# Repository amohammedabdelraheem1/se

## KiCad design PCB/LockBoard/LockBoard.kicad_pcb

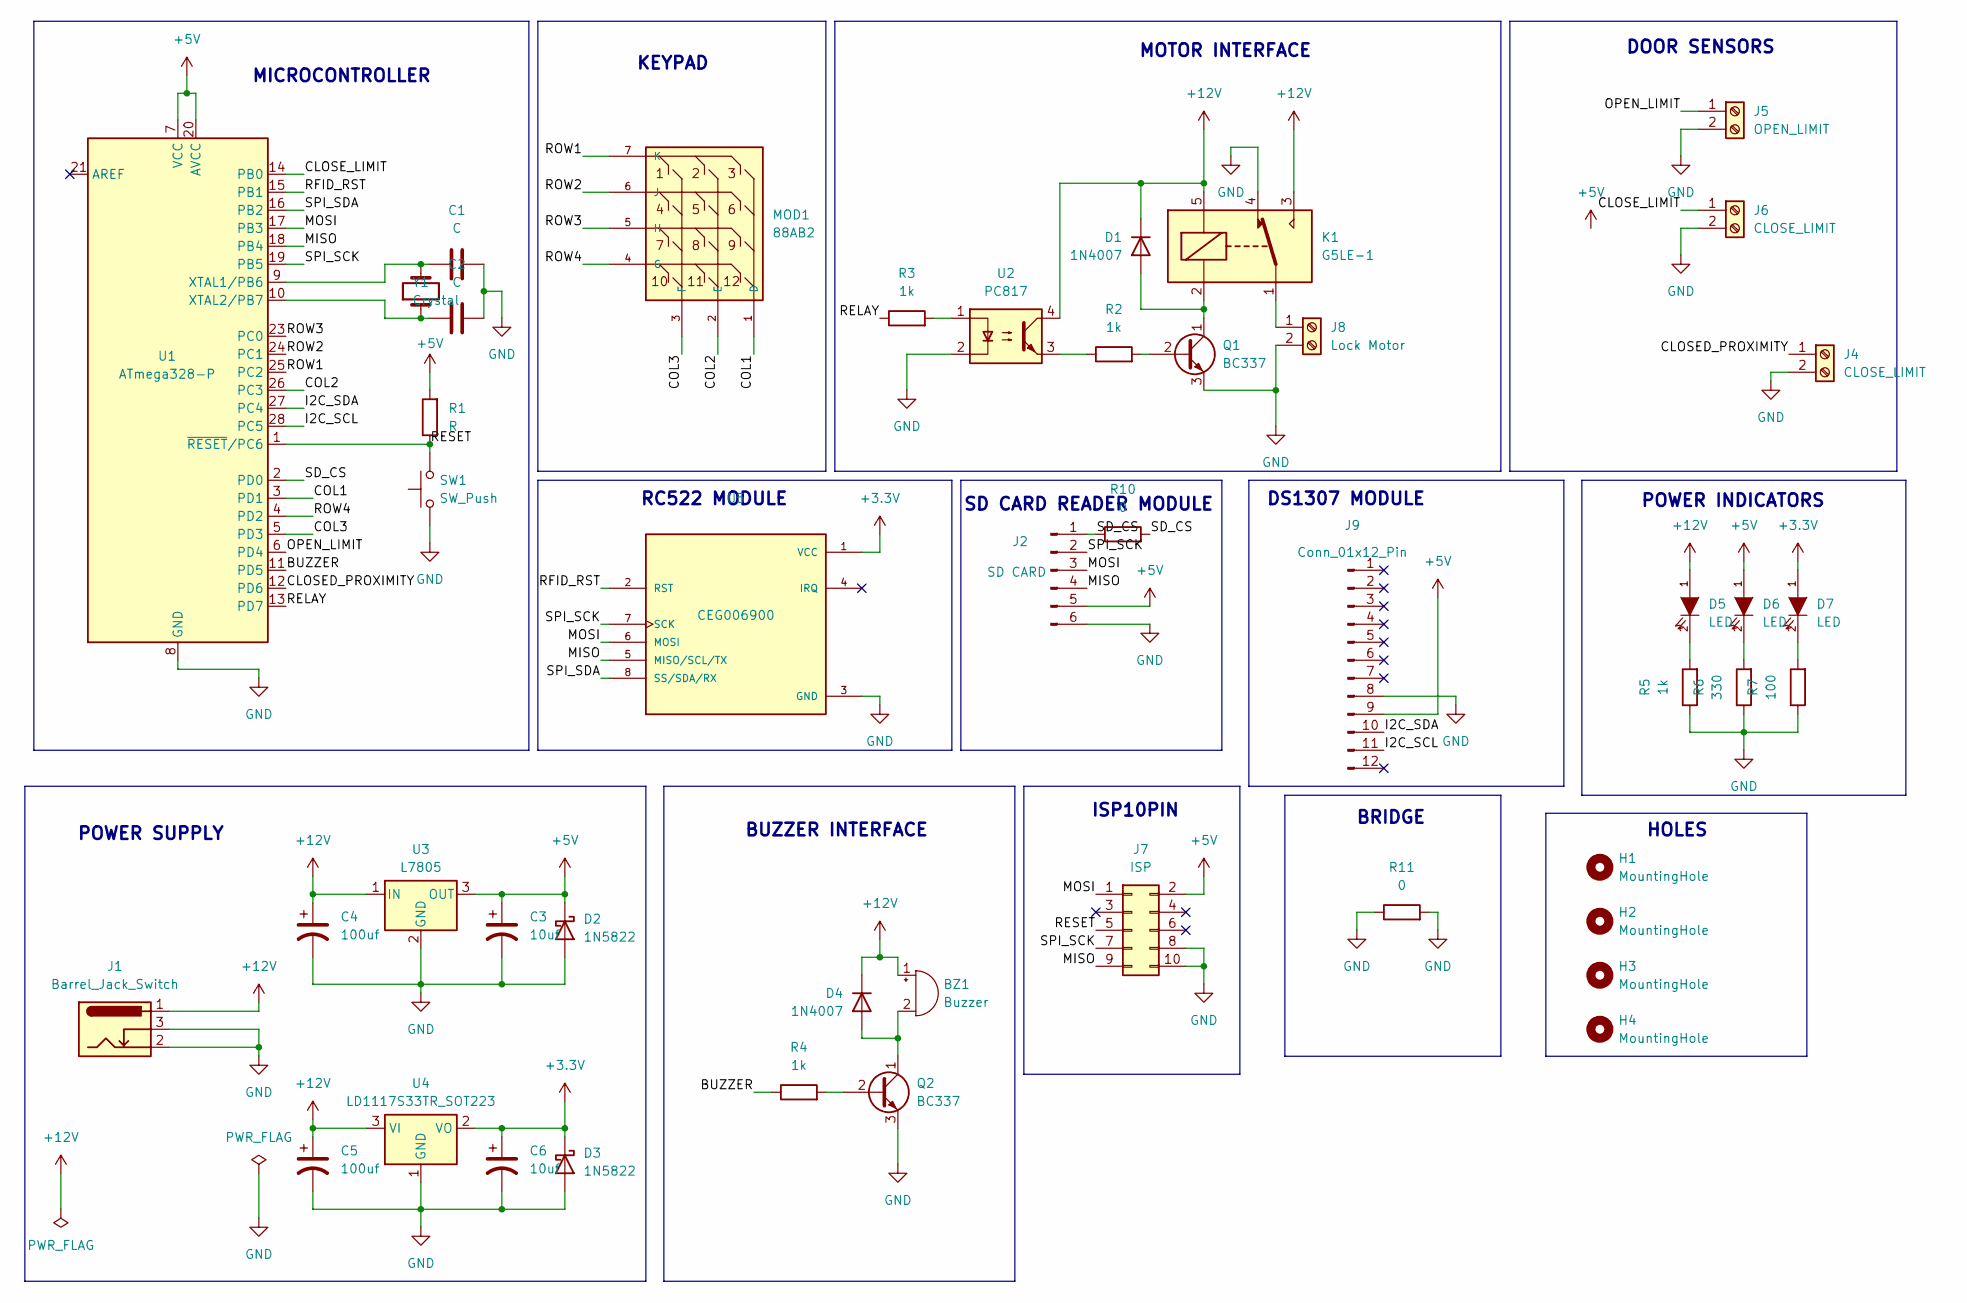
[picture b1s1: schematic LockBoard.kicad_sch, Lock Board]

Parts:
BZ1: Buzzer; Buzzer_12x9.5RM7.6
C1, C2: C; C_Disc_D4.3mm_W1.9mm_P5.00mm
C3, C6: 10uf; CP_Radial_D5.0mm_P2.50mm
C4, C5: 100uf; CP_Radial_D8.0mm_P2.50mm
D1, D4: 1N4007; D_DO-41_SOD81_P10.16mm_Horizontal
D2, D3: 1N5822; D_DO-201AD_P15.24mm_Horizontal
D5, D6, D7: LED; LED_D3.0mm
H1, H2, H3, H4: MountingHole; MountingHole_4.3mm_M4_ISO14580
J1: Barrel_Jack_Switch; BarrelJack_Horizontal
J2: SD CARD; SD_Card_Module
J4, J6: CLOSE_LIMIT; TerminalBlock_Phoenix_MKDS-1,5-2_1x02_P5.00mm_Horizontal
J5: OPEN_LIMIT; TerminalBlock_Phoenix_MKDS-1,5-2_1x02_P5.00mm_Horizontal
J7: ISP; IDC-Header_2x05_P2.54mm_Vertical
J8: Lock Motor; TerminalBlock_Phoenix_MKDS-1,5-2_1x02_P5.00mm_Horizontal
J9: Conn_01x12_Pin; Tiny_RTC_DS1307
K1: G5LE-1; Relay_SPDT_Omron-G5LE-1
MOD1: 88AB2; JST_XH_S7B-XH-A-1_1x07_P2.50mm_Horizontal
Q1, Q2: BC337; TO-92_Inline
R1: R; R_Axial_DIN0207_L6.3mm_D2.5mm_P7.62mm_Horizontal
R2, R3, R4, R5: 1k; R_Axial_DIN0207_L6.3mm_D2.5mm_P7.62mm_Horizontal
R6: 330; R_Axial_DIN0207_L6.3mm_D2.5mm_P7.62mm_Horizontal
R7: 100; R_Axial_DIN0207_L6.3mm_D2.5mm_P7.62mm_Horizontal
R10, R11: 0; R_Axial_DIN0207_L6.3mm_D2.5mm_P7.62mm_Horizontal
SW1: SW_Push; SW_PUSH_6mm
U1: ATmega328-P; DIP-28_W7.62mm
U2: PC817; DIP-4_W7.62mm
U3: L7805; TO-220-3_Vertical
U4: LD1117S33TR_SOT223; TO-220-3_Vertical
U5: CEG006900; JST_XH_S8B-XH-A-1_1x08_P2.50mm_Horizontal; PARTREV 12 June 2019
Y1: Crystal; Crystal_HC49-4H_Vertical

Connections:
+3.3V: C6.1, D3.1 (K), D7.1 (A), U4.2 (VO), U5.1 (VCC)
+5V: C3.1, D2.1 (K), D6.1 (A), J2.5, J7.2, J9.9, R1.2, U1.7 (VCC), U1.20 (AVCC), U3.3 (OUT)
+12V: BZ1.1 (+), C4.1, C5.1, D1.1 (K), D4.1 (K), D5.1 (A), J1.1, K1.3, K1.5, U2.4, U3.1 (IN), U4.3 (VI)
/BUZZER: R4.1, U1.11 (PD5)
/CLOSED_PROXIMITY: J4.1, U1.12 (PD6); also elsewhere on the board
/CLOSE_LIMIT: J6.1, U1.14 (PB0)
/COL1: MOD1.1 (D), U1.3 (PD1)
/COL2: MOD1.2 (E), U1.26 (PC3)
/COL3: MOD1.3 (F), U1.5 (PD3)
/I2C_SCL: J9.11, U1.28 (PC5)
/I2C_SDA: J9.10, U1.27 (PC4)
/MISO: J2.4, J7.9, U1.18 (PB4), U5.5 (MISO/SCL/TX)
/MOSI: J2.3, J7.1, U1.17 (PB3), U5.6 (MOSI)
/OPEN_LIMIT: J5.1, U1.6 (PD4)
/RELAY: R3.1, U1.13 (PD7)
/RESET: J7.5, R1.1, SW1.2, U1.1 (~RESET/PC6)
/RFID_RST: U1.15 (PB1), U5.2 (RST)
/ROW1: MOD1.7 (K), U1.25 (PC2)
/ROW2: MOD1.6 (J), U1.24 (PC1)
/ROW3: MOD1.5 (H), U1.23 (PC0)
/ROW4: MOD1.4 (G), U1.4 (PD2)
/SD_CS: J2.1, R10.1, R10.2, U1.2 (PD0)
/SPI_SCK: J2.2, J7.7, U1.19 (PB5), U5.7 (SCK)
/SPI_SDA: U1.16 (PB2), U5.8 (SS/SDA/RX)
GND: C1.2, C2.2, C3.2, C4.2, C5.2, C6.2, D2.2 (A), D3.2 (A), J1.2, J1.3, J2.6, J4.2, J5.2, J6.2, J7.8, J7.10, J8.2, J9.8, K1.4, Q1.3 (E), Q2.3 (E), R5.1, R6.1, R7.1, R11.1, R11.2, SW1.1, U1.8 (GND), U1.22 (GND), U2.2, U3.2 (GND), U4.1 (GND), U5.3 (GND); also elsewhere on the board
unnamed: BZ1.2 (-), D4.2 (A), Q2.1 (C)
unnamed: D1.2 (A), K1.2, Q1.1 (C)
unnamed: D5.2 (K), R5.2
unnamed: D6.2 (K), R6.2
unnamed: D7.2 (K), R7.2
unnamed: J8.1, K1.1
unnamed: Q1.2 (B), R2.2
unnamed: Q2.2 (B), R4.2
unnamed: R2.1, U2.3
unnamed: R3.2, U2.1
unnamed: C1.1, U1.9 (XTAL1/PB6), Y1.2
unnamed: C2.1, U1.10 (XTAL2/PB7), Y1.1

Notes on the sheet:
MOTOR INTERFACE
HOLES
BRIDGE
POWER SUPPLY
POWER INDICATORS
ISP10PIN
BUZZER INTERFACE
DOOR SENSORS
SD CARD READER MODULE
RC522 MODULE
DS1307 MODULE
MICROCONTROLLER
KEYPAD

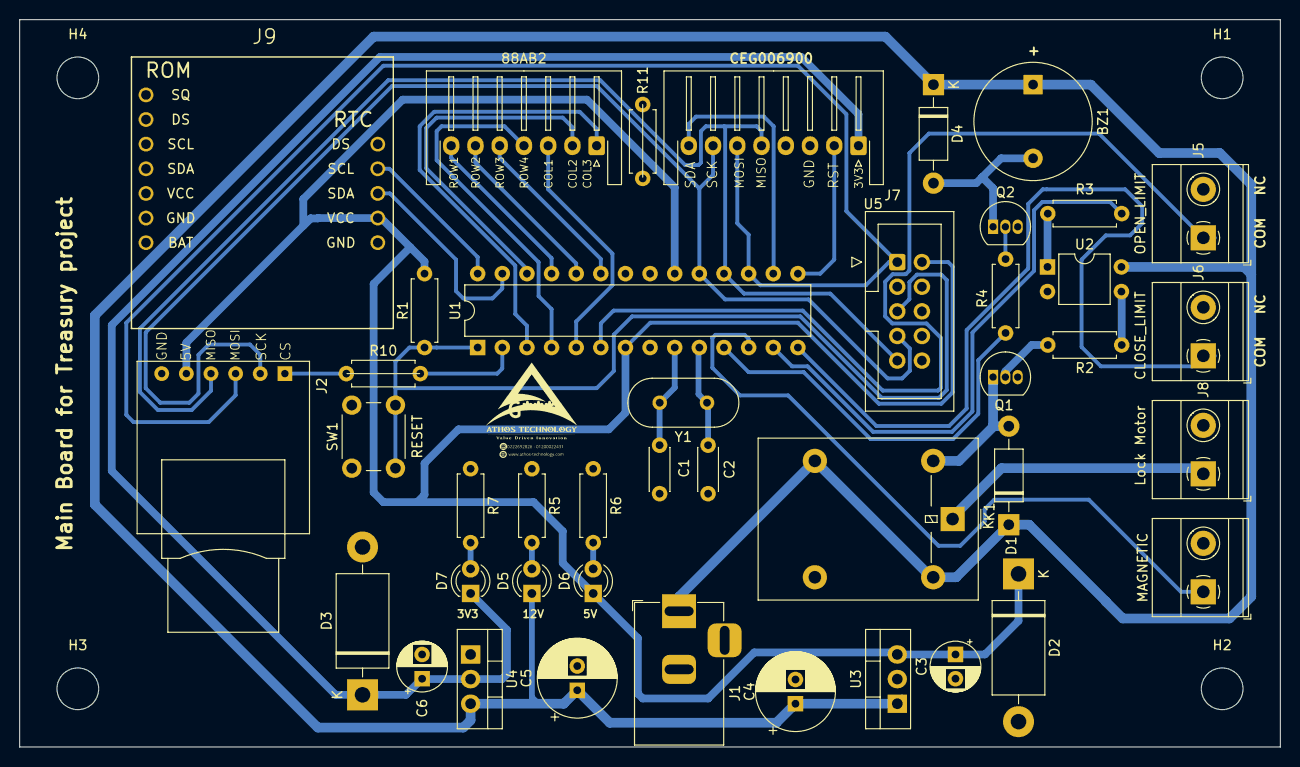
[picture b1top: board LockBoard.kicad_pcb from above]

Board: 2 copper layers, 130.0 x 75.0 mm, 46 parts (0 on the bottom side), 37 nets.

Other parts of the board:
MAGNETIC: CLOSE_LIMIT; TerminalBlock_Phoenix_MKDS-1,5-2_1x02_P5.00mm_Horizontal

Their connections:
/CLOSED_PROXIMITY: MAGNETIC.1; also elsewhere on the board
GND: MAGNETIC.2; also elsewhere on the board

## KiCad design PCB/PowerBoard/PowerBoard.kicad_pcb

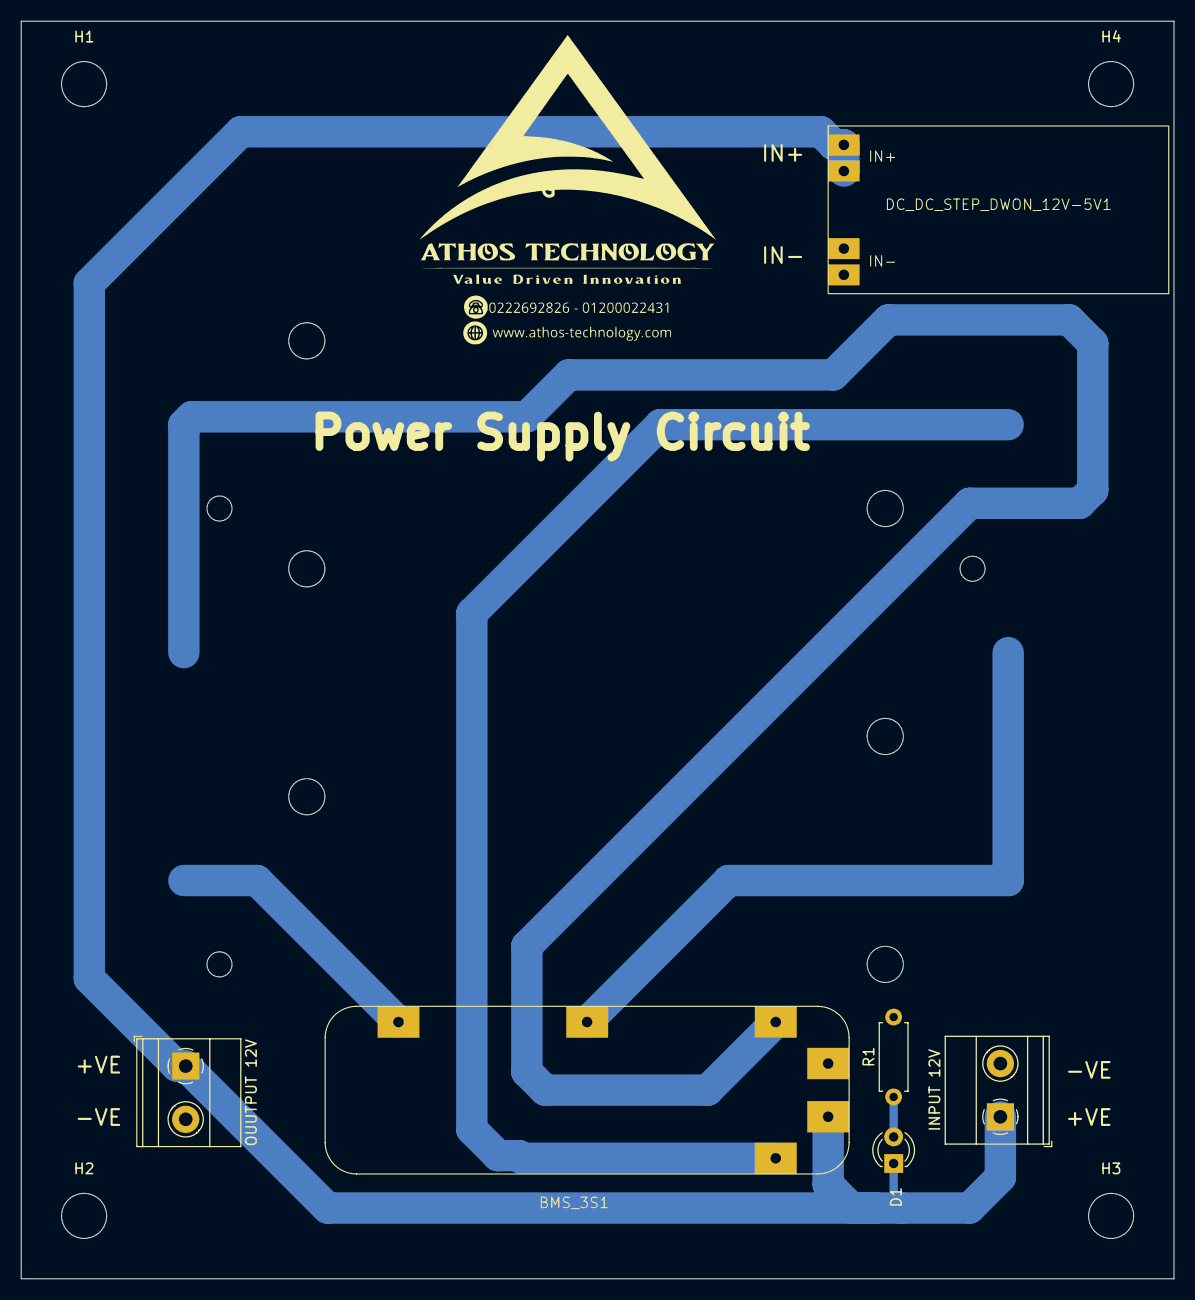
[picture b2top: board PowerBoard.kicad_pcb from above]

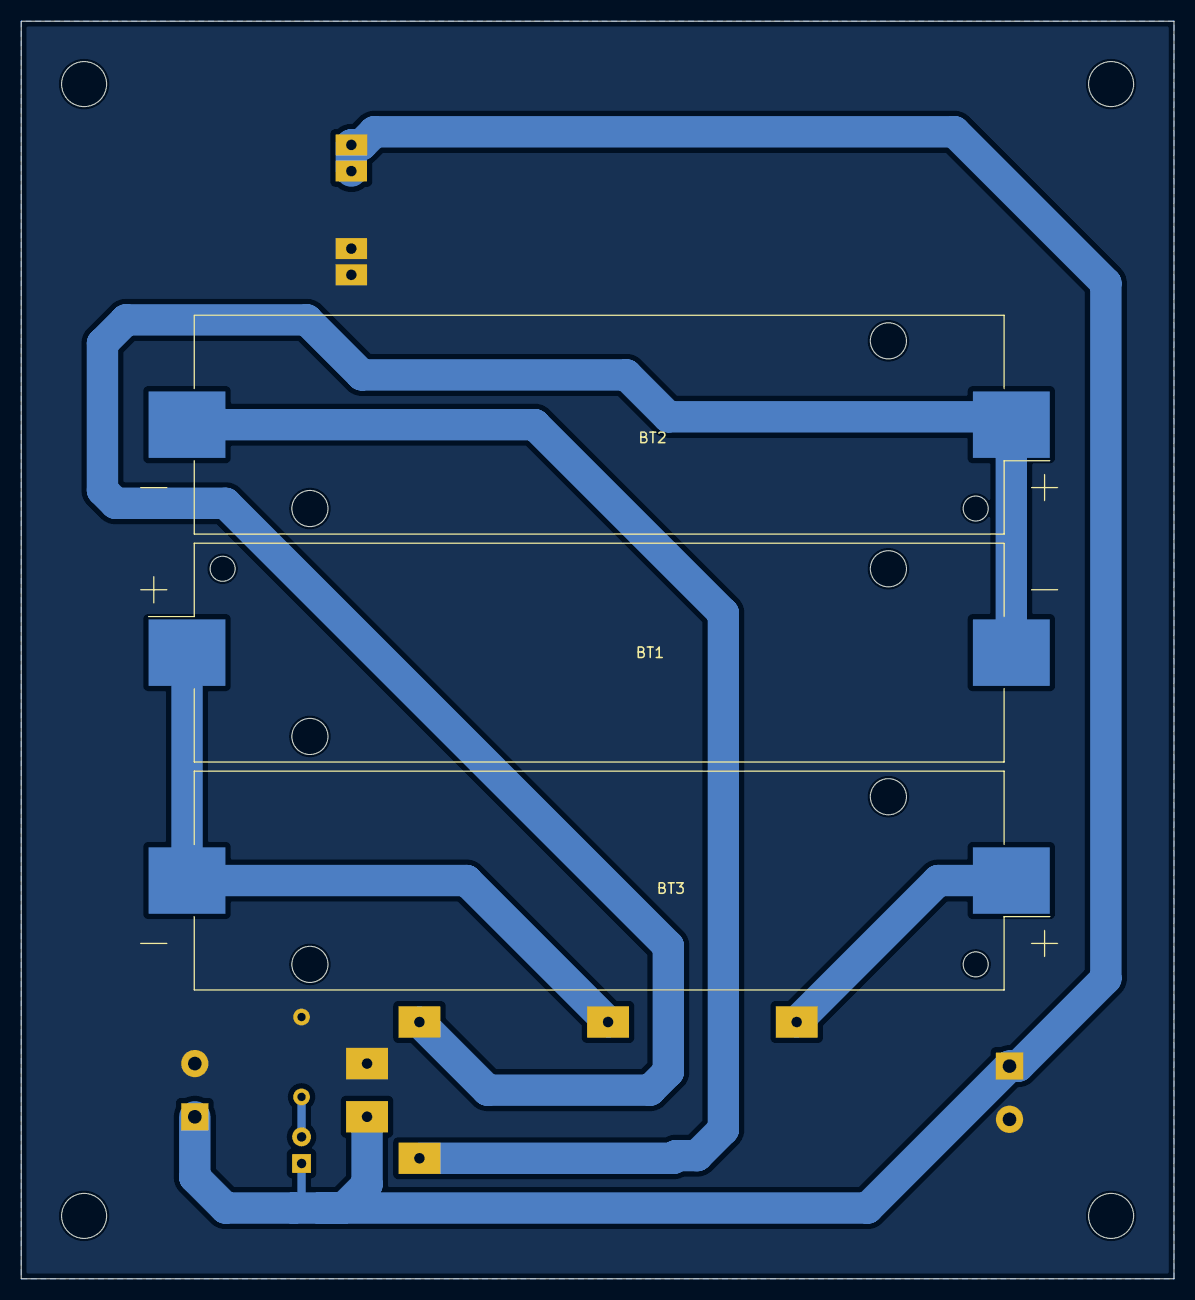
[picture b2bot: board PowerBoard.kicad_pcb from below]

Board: 2 copper layers, 110.0 x 120.0 mm, 13 parts (3 on the bottom side), 7 nets.

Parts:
BMS_3S1: BMS_3S
BT1, BT2, BT3: Battery_Cell; BatteryHolder_Keystone_1042_1x18650
D1: LED; LED_D3.0mm
DC_DC_STEP_DWON_12V-5V1: DC_DC_STEP_DOWN_12V-5V
H1, H2, H3, H4: MountingHole; MountingHole_4.3mm_M4_ISO14580
INPUT 12V: IN; TerminalBlock_Phoenix_MKDS-1,5-2-5.08_1x02_P5.08mm_Horizont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
OUUTPUT 12V: OUT; TerminalBlock_Phoenix_MKDS-1,5-2-5.08_1x02_P5.08mm_Horizont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
R1: R; R_Axial_DIN0207_L6.3mm_D2.5mm_P7.62mm_Horizontal

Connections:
+12V: BMS_3S1.6 (P+), D1.1 (A), DC_DC_STEP_DWON_12V-5V1.1 (in+), INPUT 12V.1, OUUTPUT 12V.1
GND: BMS_3S1.5 (P-), DC_DC_STEP_DWON_12V-5V1.2 (in-), INPUT 12V.2, OUUTPUT 12V.2, R1.2
unnamed: BMS_3S1.2 (B1), BT1.1 (+), BT2.2 (-)
unnamed: BMS_3S1.3 (B2), BT2.1 (+), BT3.2 (-)
unnamed: BMS_3S1.4 (B+), BT3.1 (+)
unnamed: BMS_3S1.1 (B-), BT1.2 (-)
unnamed: D1.2 (K), R1.1

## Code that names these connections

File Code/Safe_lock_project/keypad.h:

/******************************************************************************
*
* Module: KEYPAD
*
* File Name: keypad.h
*
* Description: Header file for the Keypad driver
*
* Author: Ahmed Mohammed Abdelraheem
*
*******************************************************************************/

#ifndef KEYPAD_H_
#define KEYPAD_H_
#include <Arduino.h>
// Preprocessor directive to ensure C++ compatibility
// Prevents name mangling when used in C++ projects
#ifdef __cplusplus
extern "C" {
#endif   //__cplusplus

/*******************************************************************************
 *                                Definitions                                  *
 *******************************************************************************/

/* Keypad configurations for number of rows and columns */
#define KEYPAD_NUM_COLS                   3 // Number of columns in the keypad
#define KEYPAD_NUM_ROWS                   4 // Number of rows in the keypad
#define KEYPAD_DEBOUNCING_NUM             5 // Number of times to debounce the keypad
#define NONPRESSED                        0xFF // Value returned when no key is pressed             

/* Keypad pin Configurations */
#define KEYPAD_ROW1_PIN                   2  // PD2 (Pin 2)
#define KEYPAD_ROW2_PIN                   14 // PC0 (Pin 14)
#define KEYPAD_ROW3_PIN                   15 // PC1 (Pin 3)
#define KEYPAD_ROW4_PIN                   17 // A3 PC3 (Pin 17)
#define KEYPAD_COL1_PIN                   3 // PD3 (Pin 3)
#define KEYPAD_COL2_PIN                   0 // PD1 (Pin 1)---------------->
#define KEYPAD_COL3_PIN                   16 // PC2 (Pin 16)

/* Keypad button logic configurations */
#define KEYPAD_BUTTON_PRESSED            LOW // Logic level when a button is pressed
#define KEYPAD_BUTTON_RELEASED           HIGH // Logic level when a button is released

/*******************************************************************************
 *                      Functions Prototypes                                   *
 *******************************************************************************/

/*
 * Description :
 * Get the Keypad pressed button
 */
uint8_t KEYPAD_getPressedKey(void); // Function prototype for getting the pressed key
uint8_t KEYPAD_getPressedNewKey(void);
#ifdef __cplusplus
}
#endif   //__cplusplus
#endif /* KEYPAD_H_ */

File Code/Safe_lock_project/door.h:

// Header guard to prevent multiple inclusions
#ifndef DOOR_H_
#define DOOR_H_

// Extern "C" block to ensure compatibility with C++ compilation
#ifdef __cplusplus
extern "C" {
#endif
#define MOTOR_MAX_ON_TIME_MS 2000
//************************    Pins connection    *****************************/
// Pin definitions for limit switches 
// Indicates the microcontroller pins used for detecting lock's open and closed positions
#define CLOSE_LIMIT_PIN   5 //PD5 - Pin for close limit switch
#define OPEN_LIMIT_PIN    8 //PB0 - Pin for open limit switch

// Pin definition for proximity sensor
#define PROXIMITY_PIN     4   //PD4 (Pin D4)
#define DUBOUNCING_COUNTER  2

// Defines possible states for the lock
// Provides a clear representation of the lock's current position
typedef enum {
    LOCK_UNKNOWN,  // Initial state or when position cannot be determined
    LOCK_OPEN,     // Lock is in fully open position
    LOCK_CLOSED    // Lock is in fully closed position
} tLock_state;

// Enumeration to represent door states
typedef enum {
  DOOR_OPEN,   // Door is open
   DOOR_CLOSED  // Door is closed
} tDoor_state;

// Static variable to track current door state
// Note: There's a typo in the type (tLDoor_state instead of tDoor_state)
static tDoor_state s_door_state = DOOR_OPEN;

// Function declarations for door control
void Door_Init(void);       // Initialize door system
void Door_Update(void);     // Update door state
tDoor_state Door_GetState(void);  // Retrieve current door state
tLock_state Door_Lock_GetState(void); // Lock the door
void Door_Lock(void);
void Door_Unlock(void);
void DoorDisplay(void);

// Close extern "C" block for C++ compatibility
#ifdef __cplusplus
}
#endif

#endif  //DOOR_H_

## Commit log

2025-07-10 init commit
2025-07-21 Lock and rfid tested open lock at setup and lock the door when it is closed motor rotate Mx 2sec
2025-07-24 temp commit
2025-07-24 temp2
2025-07-24 implement all modules in cpp and h file error compiling for arduino
2025-07-25 final implementation of modules ini .cpp and .h files without any errors
2025-07-25 final implementation of modules ini .cpp and .h files without any errors2
2025-07-25 keypad with double debouncing check
2025-08-01 Modefirstcommit
